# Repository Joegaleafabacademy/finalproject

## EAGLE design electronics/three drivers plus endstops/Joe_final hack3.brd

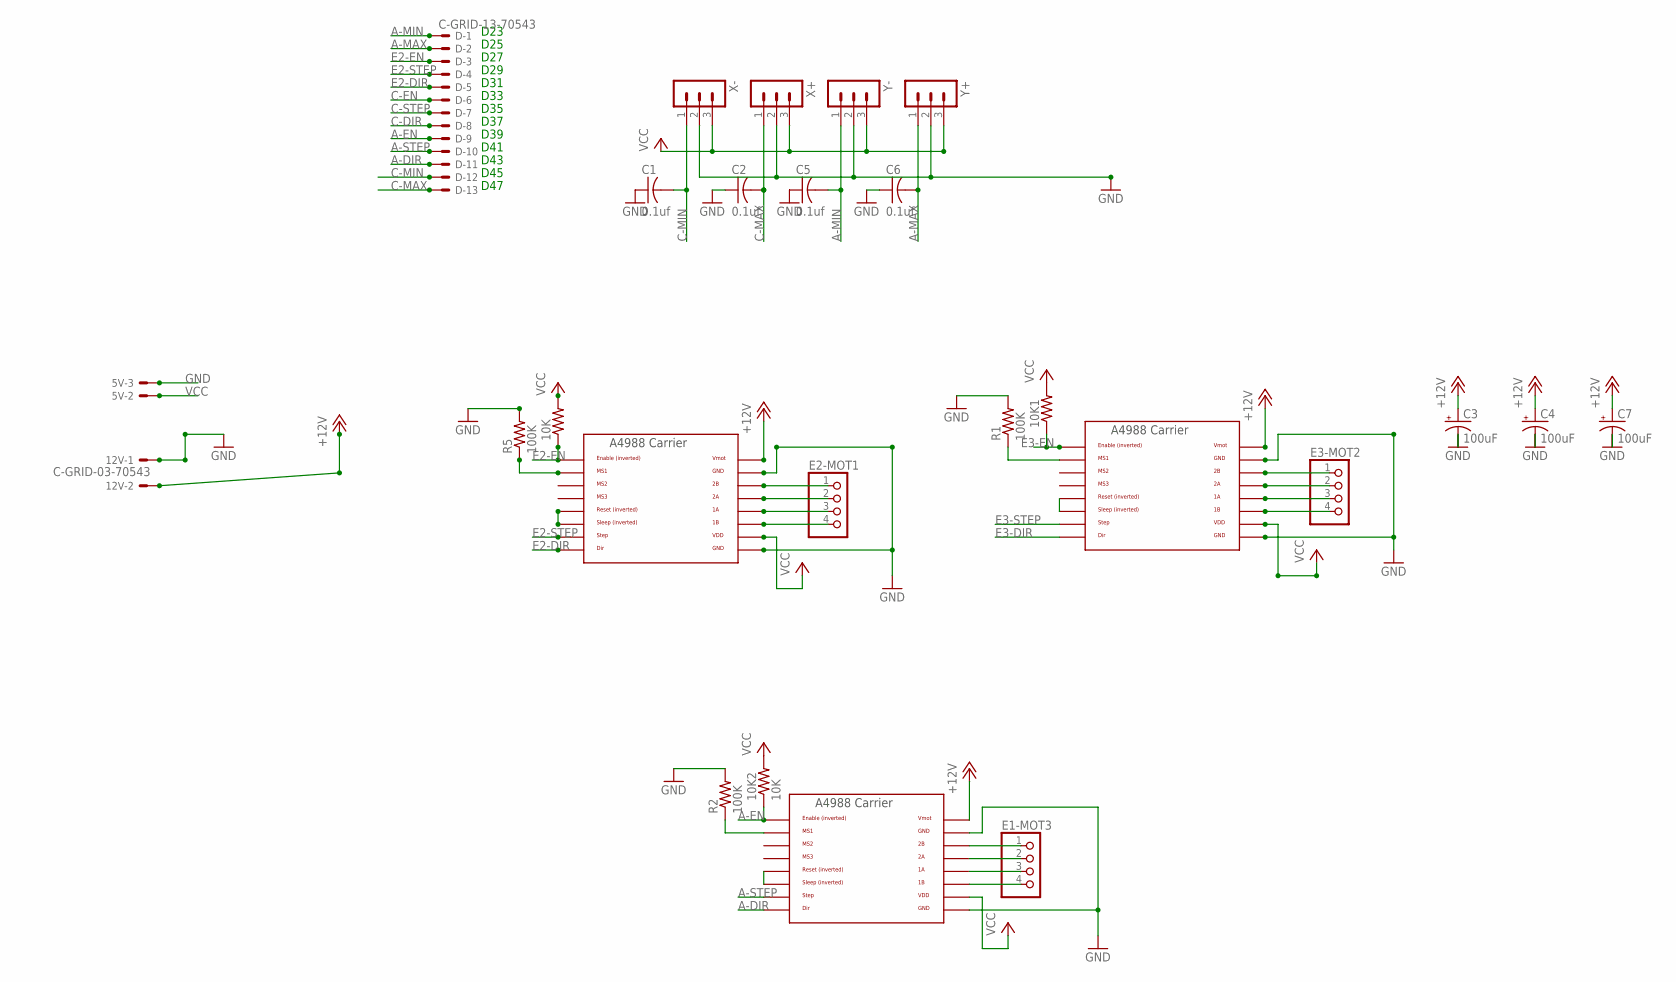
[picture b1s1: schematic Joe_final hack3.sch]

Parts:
5V, 12V: C-GRID-03-70543; 70543-03
10K, 10K1: RES-US1206FAB; R1206FAB
10K2: 10K; R1206FAB
C1, C2, C5, C6: 0.1uf; C1206FAB
C3, C4, C7: 100uF; 153CLV-0605
D: C-GRID-13-70543; 70543-13
E1-MOT3, E2-MOT1, E3-MOT2: PINHD-1X4; 1X04
R1, R2, R5: 100K; R1206FAB
U$1, U$4, U$5: A4988BREAKOUT
X+: 3PIN-HEADER
X-: 3PIN-HEADER
Y+: 3PIN-HEADER
Y-: 3PIN-HEADER

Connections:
+12V: 12V.2, C3.+, C4.+, C7.+, U$1.VMOT, U$4.VMOT, U$5.VMOT
A-DIR: D.11, U$1.DIR
A-EN: 10K2.1, D.9, U$1.EN
A-MAX: C6.2, D.2, Y+.1
A-MIN: C5.2, D.1, Y-.1
A-STEP: D.10, U$1.STEP
C-DIR: D.8
C-EN: D.6
C-MAX: C2.2, D.13, X+.1
C-MIN: C1.2, D.12, X-.1
C-STEP: D.7
E2-DIR: D.5, U$4.DIR
E2-EN: 10K.1, D.3, U$4.EN
E2-STEP: D.4, U$4.STEP
E3-DIR: U$5.DIR
E3-EN: 10K1.1, U$5.EN
E3-STEP: U$5.STEP
GND: 5V.3, 12V.1, C1.1, C2.1, C3.-, C4.-, C5.1, C6.1, C7.-, R1.2, R2.2, R5.2, U$1.GND, U$1.GND@0 (GND), U$4.GND, U$4.GND@0 (GND), U$5.GND, U$5.GND@0 (GND), X+.2, X-.2, Y+.2, Y-.2
unnamed: E1-MOT3.1, U$1.2B
unnamed: U$1.RST, U$1.SLP (SLEEP)
unnamed: E1-MOT3.2, U$1.2A
unnamed: E2-MOT1.1, U$4.2B
unnamed: R5.1, U$4.MS1
unnamed: E1-MOT3.3, U$1.1A
unnamed: R2.1, U$1.MS1
unnamed: U$4.RST, U$4.SLP (SLEEP)
unnamed: E1-MOT3.4, U$1.1B
unnamed: E2-MOT1.2, U$4.2A
unnamed: E2-MOT1.3, U$4.1A
unnamed: E2-MOT1.4, U$4.1B
unnamed: E3-MOT2.1, U$5.2B
unnamed: E3-MOT2.2, U$5.2A
unnamed: E3-MOT2.3, U$5.1A
unnamed: E3-MOT2.4, U$5.1B
unnamed: U$5.RST, U$5.SLP (SLEEP)
unnamed: R1.1, U$5.MS1
VCC: 5V.2, 10K.2, 10K1.2, 10K2.2, U$1.VDD, U$4.VDD, U$5.VDD, X+.3, X-.3, Y+.3, Y-.3

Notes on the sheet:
D23
D25
D27
D29
D31
D33
D35
D37
D39
D41
D43
D45
D47

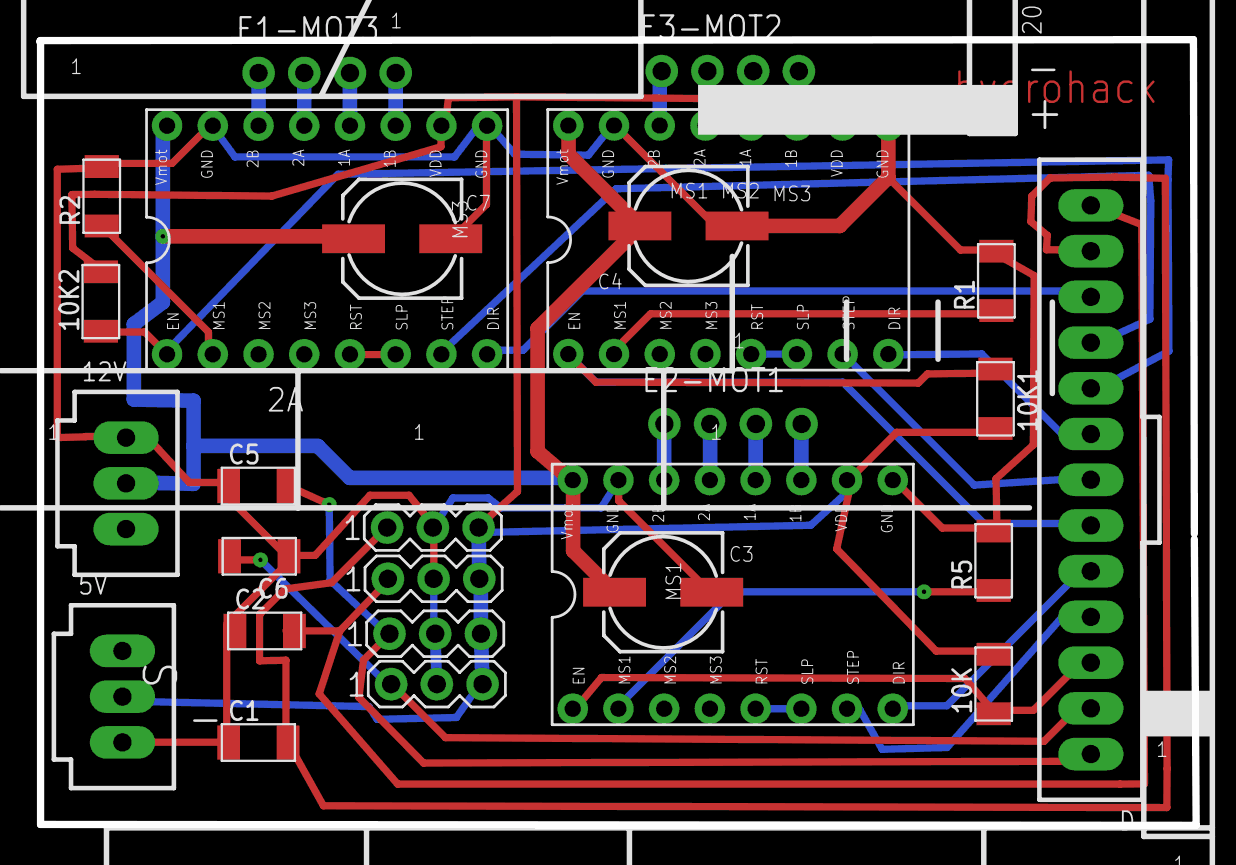
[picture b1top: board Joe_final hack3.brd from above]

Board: 2 copper layers, 64.2 x 43.6 mm, 26 parts (0 on the bottom side), 32 nets.

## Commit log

2016-07-02 final files
